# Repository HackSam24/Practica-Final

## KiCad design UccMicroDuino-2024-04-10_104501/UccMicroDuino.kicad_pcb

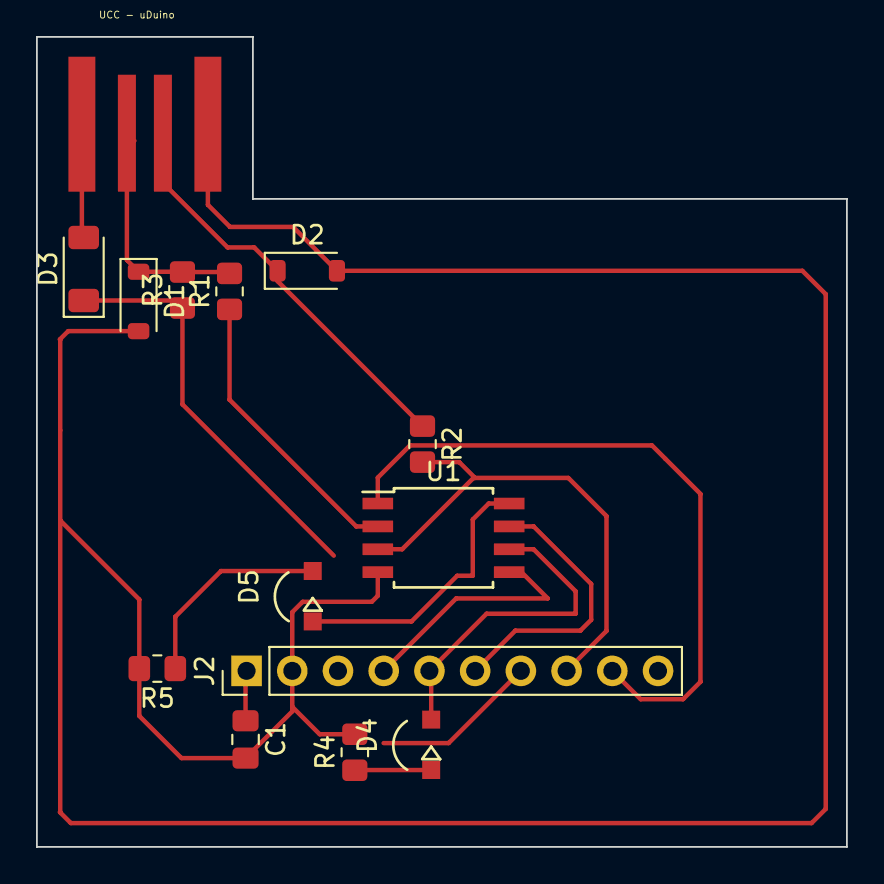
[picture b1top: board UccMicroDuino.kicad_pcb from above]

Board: 2 copper layers, 45.0 x 45.0 mm, 14 parts (0 on the bottom side), 13 nets.

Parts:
C1: 0.1u; C_0805_2012Metric_Pad1.18x1.45mm_HandSolder
D1, D2: 3.6v 1/2mW; D_SOD-123
D3: PMLL4148L; D_MiniMELF
D4: Led Green; ledSMD
D5: Led Red; ledSMD
J1: USB_PCB_A; USB_A_UCC
J2: Header; PinHeader_1x10_P2.54mm_Vertical
R1, R2: 68Ω 5% 1/8W; R_0805_2012Metric_Pad1.20x1.40mm_HandSolder
R3: 1.5kΩ 5% 1/8W; R_0805_2012Metric_Pad1.20x1.40mm_HandSolder
R4, R5: 330Ω 5% 1/8W; R_0805_2012Metric_Pad1.20x1.40mm_HandSolder
U1: ATtiny85-20SU; SOIC-8W_5.3x5.3mm_P1.27mm

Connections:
+5V: C1.1, D3.1 (K), D5.1 (K), J2.1, R3.1, U1.8 (VCC)
GND: C1.2, D1.2 (A), D2.2 (A), J1.4 (GND), J2.2, R4.2, R5.2, U1.4 (GND)
unnamed: D1.1 (K), J1.2 (D-), R1.2, R3.2
unnamed: D2.1 (K), J1.3 (D+), R2.1
unnamed: D3.2 (A), J1.1 (VBUS)
unnamed: D4.2 (A), J2.5, U1.6 (PB1)
unnamed: D4.1 (K), R4.1
unnamed: D5.2 (A), R5.1
unnamed: J2.4, U1.5 (AREF/PB0)
unnamed: J2.6, U1.7 (PB2)
unnamed: J2.7, R1.1, U1.2 (XTAL1/PB3)
unnamed: J2.8, R2.2, U1.3 (XTAL2/PB4)
unnamed: J2.9, U1.1 (~RESET/PB5)
